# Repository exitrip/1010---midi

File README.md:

# 1010---midi
Trying organize an otherwise un-organized repo for public consumption:

## Overview
This repo contains everything one needs to repurpose an "iTrip 1G Nano" as a generic radio transmitter, including an adaptor circuit board to simplify the hack, and a "headless" Arduino program to flash firmware on to the iTrip's LPC936 microcontroller.

See the `kicad` directory for a partial schematic of the iTrip and the complete schematic and layout of the adaptor PCB.  I've got lots of the PCBs, so please ask me to send you some instead of making your own for now.

### Required supplies
If you want to replicate this work you'll need:
- iTrips (again ask me for some, I've got hundreds).  It's good to have plenty of extras for a workshop.
- an Arduino and homemade programming cable
- Soldering equipment, wire cutters, a small screw driver helps, etc.
- ~1m electrical wire per transmitter
- to pick a power source for the iTrip:
  - 2x AA/AAA battery pack, try finding them from surplus sites like [Goldmine Electronics](https://theelectronicgoldmine.com/products/g27885?_pos=18&_sid=e9574ebc7&_ss=r)
  - TO-92 or SOT23-5 3.3V, 100mA regulator (e.g. [L78L33ACZ](https://www.digikey.com/en/products/detail/stmicroelectronics/L78L33ACZ/1038304))
  - or the [FTDI FT232RL](https://www.digikey.com/en/products/detail/ftdi-future-technology-devices-international-ltd/FT232RL-REEL/1836385)  USB-to-UART converter with onboard regulator.  This chip is relatively fine pitch SMT TSSOP, so it will be challenging to seat without the right soldering tools and experience.  

A quick note about the FTDI chip:  Seating this chip will allow you to send and recieve MIDI (via serial) commands to the transmitter over USB, in fact each FTDI chip can drive up to 8 transmitters, but there are undocumented details as to how to set this up.  All of the PurrData patches, touchOSC setup, and most of the uVision code target custom modular hardware that is also poorly documented and out of scope of a workshop.  Even without the "onboard" FTDI, you can access all this functionality by using any [3.3V USB-Serial cable](https://www.adafruit.com/product/70) hooked up to the TX/RX on the adpator PCB. Reach out, I happy to discuss further.

Another note about firmware:  The LPC936 firmware programmed by the Arduino is stored in the Arduino firmware directly.  Recompiling new firmware unfortunately requires a licensed copy of KEIL uVision Cx51, which is thousands of dollars last I checked.  The "free" versions of uVision have a prohibitively small size limit, and cannot build the code as is.  I'm still investigating if I can strip the project enough...

### Setting up the programmer
See [README](arduino/exitrip_flash_programmer/README.md) in arduino folder.

## Steps for the hack
- Open up the iTrip.  Easiest way is to slip a flat head above the button and pry the plastic case open like an oyster.  Be a bit careful with the button though.
- Don't put too much stress on the cables inside the now opened iTrip, they can easily break off the PCB.
- Break the connectors from the front plastic shell.  This takes some practice, and there's maybe half a dozen ways to do this.  Notice that there's a seam in the front plastic around connectors, just under the FCC ID number.  Pressing the smaller plastic piece out of the front cover is easy, most of the time.  You can also just cut the front cover up too.
- Cut loose the antenna (black wire soldered, ANT2, to the board closest to the USB port, J3) and push the wire loose out the back of the black plastic

- Solder ~1m of wire to the antenna, this is now a [1/4 whip antenna](https://en.wikipedia.org/wiki/Whip_antenna) at ~75MHz. It's good to cheat it shorter than 1m, as that tunes it up the FM spectrum, but don't go longer.
- Connect the programming cable to the iTrip and Arduino.  Make sure the external power supply PCB is DISCONNECTED from the iTrip to be programmed.
- Power on or RESET the Arduino.  At boot up it will blink slowly, but when it successfully handshakes with the LPC936, the LED will start blinking faster during programming.  Wait until the LED is blinking slow again, which indicates programming is complete.  This is a good time to test the iTrip without the added power supply, as it will recieve power from the Arduino programmer directly.  The iTrip itself is working and correctly programmed if:
  - The red LED in the corner comes on solid 
  - The red LED turns on and off with a middle button press (this turns the transmitter on and off)
  - While the LED is on there's a signal (silence) on 87.9 MHz (every time the iTrip boots up the transmission freqency is reset to 87.9)
  - Pressing the up and down buttons, tunes the transmitter up and down.
- This step can be done at anytime, but once you've tested the iTrip works while connected to the Arduino, you can be sure that further problems are caused by the power supply.
  - Solder the desired power supply to the adaptor PCB (e.g. GND to battery negative, 3.3V to battery positive).  Any of the ICs will take 5V from either the 5V header on the adaptor or the USB port on the iTrip.  A useful 5V and 3.3V will come OUT of those headers too!

  ## Suggestions about workshops
  - FM radios are not as common as they used to be.  BRING SOME, otherwise there's a big sad trombone at the end of the build
  - Have an SDR reciever setup on a laptop to visualize the transmissions.  It will also double as a reciever.  These turnkey [RTL-SDR kits](https://www.rtl-sdr.com/buy-rtl-sdr-dvb-t-dongles/) are awesome for the price.

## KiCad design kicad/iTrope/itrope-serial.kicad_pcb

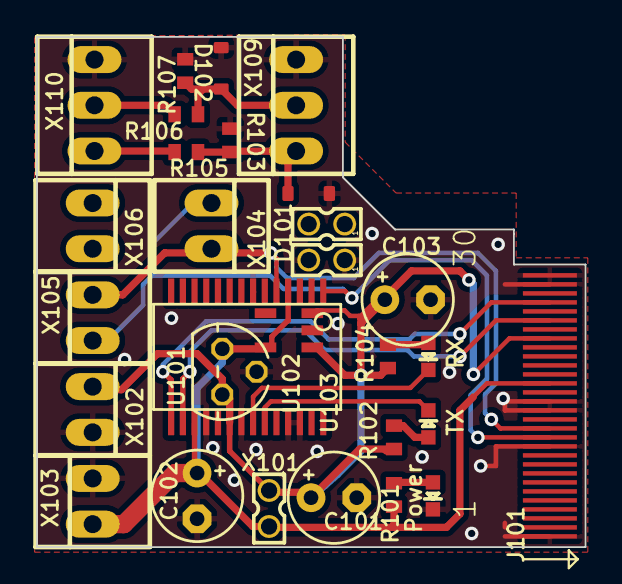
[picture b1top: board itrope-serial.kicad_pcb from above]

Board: 2 copper layers, 30.5 x 28.3 mm, 29 parts (0 on the bottom side), 16 nets.

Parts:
C101, C102: 0.1uF; E2,5-5
C103: 10uF; E2,5-5
D101, D102: DIODESOD; SOD-323
J101: ITRIP-V1; 30PINEDGE+ITRIP
LED101: Red; LED-0603
LED102: Green; LED-0603
POWER101: Red; LED-0603
R101: 330; C0402
R102, R104: 1K; C0402
R103, R107: 10k; C0402
R105, R106: 33k; C0402
U101: 78Z; TO92
U102: SOT23-5
U103: FT232RL-BASICSSOP; SSOP28DB
X101, X107, X108: 87758-0216
X102, X103, X104, X105, X106: 22-23-2021
X109, X110: 22-23-2031

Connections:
5V: C101.+, C103.+, J101.P$23, R102.1, R104.1, U101.3 (VI), U102.1 (IN), U102.3 (EN), U103.20 (VCC), X101.1 (S), X102.1 (S)
+3V3: C102.+, J101.P$18, R101.2, U101.1 (VO), U102.5 (OUT), U103.4 (VCCIO), U103.17 (3V3OUT), X101.2 (S), X103.1 (S)
/D+: J101.P$27, U103.15 (USBDP)
/D-: J101.P$25, U103.16 (USBDM)
/LEFT: D102.1 (C), R106.2, R107.2, X109.2 (S)
/RIGHT: D101.1 (C), R103.1, R105.2, X109.1 (S)
/RXD: J101.P$13, U103.5 (RXD), X104.2 (S), X105.2 (S)
/TXD: J101.P$12, U103.1 (TXD), X104.1 (S), X105.1 (S)
GND: C101.-, C102.-, C103.-, D101.2 (A), D102.2 (A), J101.P$1, J101.P$11, J101.P$15, J101.P$16, J101.P$29, J101.P$30, POWER101.C, R103.2, R107.1, U101.2 (GND), U102.2 (GND), U103.7 (GND1), U103.18 (GND2), U103.21 (GND3), U103.25 (AGND), U103.26 (TEST), X102.2 (S), X103.2 (S), X108.1 (S), X108.2 (S), X109.3 (S), X110.3 (S)
unnamed: LED101.A, R102.2
unnamed: LED102.A, R104.2
unnamed: POWER101.A, R101.1
unnamed: LED102.C, U103.22 (RXLED)
unnamed: LED101.C, U103.23 (TXLED)
unnamed: R105.1, X110.1 (S)
unnamed: R106.1, X110.2 (S)

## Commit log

2015-12-05 initial commit for exitrip code
2015-12-05 add gitignore
2015-12-05 untrack object etc...
2015-12-06 Fix Up/Down glissandi... updateNote() didn't work with uartRX rupt completely...
2015-12-06 forgot about Blinky optins
2015-12-09 fix updown effecting both voices
2016-01-04 add happy song, some comments and fix some bugs
2016-03-26 has one meh song....
2016-03-26 first stab at songdata segregation with fixed address songBook...
2016-03-26 move linker settings from sim to EMU
2016-03-27 not working
2016-03-27 fix riff type
2016-03-28 relocation working but self prog not on emulator... atleast according to the memory view from the IDE
2016-04-06 Getting a 'set bootstat then reboot for flash magic' usb loader working
2016-04-06 remove v3 ISP
2016-04-06 fuck yeah!!! give a magic sysEX or hold midButt at power on to set bootstat -> enter flashMagic bootloader
2016-04-20 got good things going
2016-04-20 fix peace song
2016-04-20 add stereo on/off
2016-04-23 tested stereo toggle and stereo control
2016-04-29 add songrePeat flag and vexations Parts
2016-04-30 got looPsongs working with a new songFlags deal... workers can now looP on their lonesome too
2016-05-27 really slow , spread spectrum vexations only, autostart seems to work well... added a setFreq which works from boot!!! its late
2016-06-18 sump show or there about
2016-06-18 This has the boot entry disabled... cause its a killer for workshops
2016-06-18 turn LED on at boot for Power ind...
2016-06-22 bring in adc code
2016-06-22 add sin LUTs
2016-06-22 add DACout to each timer... each write to DAC is a good number of instructions
2016-07-07 add ee files
2016-07-13 first stab at adc0 and dac1 out for both coord and basics
2016-07-13 comment out playGate, cause it really bungs the interface up
2016-07-17 commit unit11 opening state
2016-09-11 ctrl-S
2016-10-05 getting working
2016-10-08 fix polarity of CV control and turn on STEREO from boot
2016-11-23 put test patches in a safe place
2016-11-26 got note creation working ok, timer overflow still broken
2016-11-26 timer overflow fixed
2016-11-27 almost got a c file... still no curly brackets...
2016-12-26 working on processing programs
2017-01-21 fix this one wierd compiler error with settings
2017-01-21 add more code space
2017-01-21 more unitXII'ing
2017-01-21 add adc03 define
2017-01-22 update adcin
2017-01-22 add interrupt garuda inside txProg() and fix glaring note->station_down bug/typo...
2017-01-23 have a robust single gate input coordinator and gate+CV input for transmitter quirky but not unusable
2017-01-25 i think we are actually erasing.... maybe its a conf bit thing....
2017-01-25 programming with 3v3 and 5V arduinos works headless atleast!!!!! add script to wrap xxd -i array
2017-01-25 crtl-s
2017-01-25 shift pinout to skip builtin led / unlucky pin
2017-01-25 ctrl-s debuggging unit modes
2017-03-23 add eagle files for cloudgods
2017-04-06 cntrl s on lots of work...
2017-04-09 freeze hive as submitted to PCBway
2017-04-09 DAC out to follow audio pitch... so that we can FM with CV
2017-04-09 actually do last commit and rm pcb folder
2017-04-09 clean up dac code a bit
2017-04-09 update LUTFreq and ???
2017-04-10 return LUTFreq and tweak timing of output interrupts... add stereo_tog to accepted external commands and ... add VNote/LNote to updateNote() ... and cleave off 256 bytes from the unused sysEx xdata b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
2017-05-18 got a ram based channel address scheme compiling
2017-05-26 add some ui to puredata stuff
2017-06-04 fix deadly pin assignment bug in mini pro code
2017-09-05 add a script that will load .hex file with to numbers that should in turn get loaded as channels
2017-09-06 script now detects and overwrites old channels
2017-09-06 add untested code in arduino programmer to insert defined midi channels dynamically
2017-09-06 update code alignment in linker, update scripts
2017-09-06 program time channel selection through arduino works!!! kinda... Lchan always responds....
2017-09-07 fixed a whole lot of minor and fatal things.... decent error checking of channels at start up and general behaviour.... arduino and script work ok...
2018-01-03 tweak eagle board and sundries
2018-03-24 add uV5 project
2018-04-04 save basic project
2018-04-04 add more visual and midi pd stuff
2018-04-22 update pd patches
2018-04-27 remove random pure-data patches
2018-04-27 working on osc control for big arrays
2018-08-12 trying to get merge to compile
2018-09-22 add new oscSwitch multi page setup
2020-02-02 push newer pd files
2020-02-02 got it compiling and hope to have fixed the note off bug
2020-02-02 add oscRouter and new polyphonic stuff... note off now twerks
2022-05-07 need to compare to whats on github
2022-05-13 add Pitch bend to L and V chan, untested
2023-09-17 just want to slurp oscRouter change, but i remember this firmware working
2023-11-25 update with headless linux setup
2023-11-25 try for duration feedback
2023-11-25 fix duration feedback
2023-11-25 remove scale feedback
2023-11-25 fix several typos
2023-11-25 sync touch and pd settings
2023-11-25 wierd that limits didnt get set in other commit
2023-11-25 found the global range loadband
2023-11-25 fix statscale response... have metroscale effect all metros live
2024-07-12 add newer, almost finished kicad schematic
2024-08-25 tweak kicad a bit
2024-08-26 got a wordy, but decent README up
2024-08-26 cleave off programmer instructions
2024-08-26 fix file rename
2024-08-26 foldres...
2024-08-26 file.s......
2024-08-26 images....
2024-08-26 spaces, and images
2024-08-29 markup png
2024-09-01 define mask out all the channel setting code that expects more complex itrip firmware
